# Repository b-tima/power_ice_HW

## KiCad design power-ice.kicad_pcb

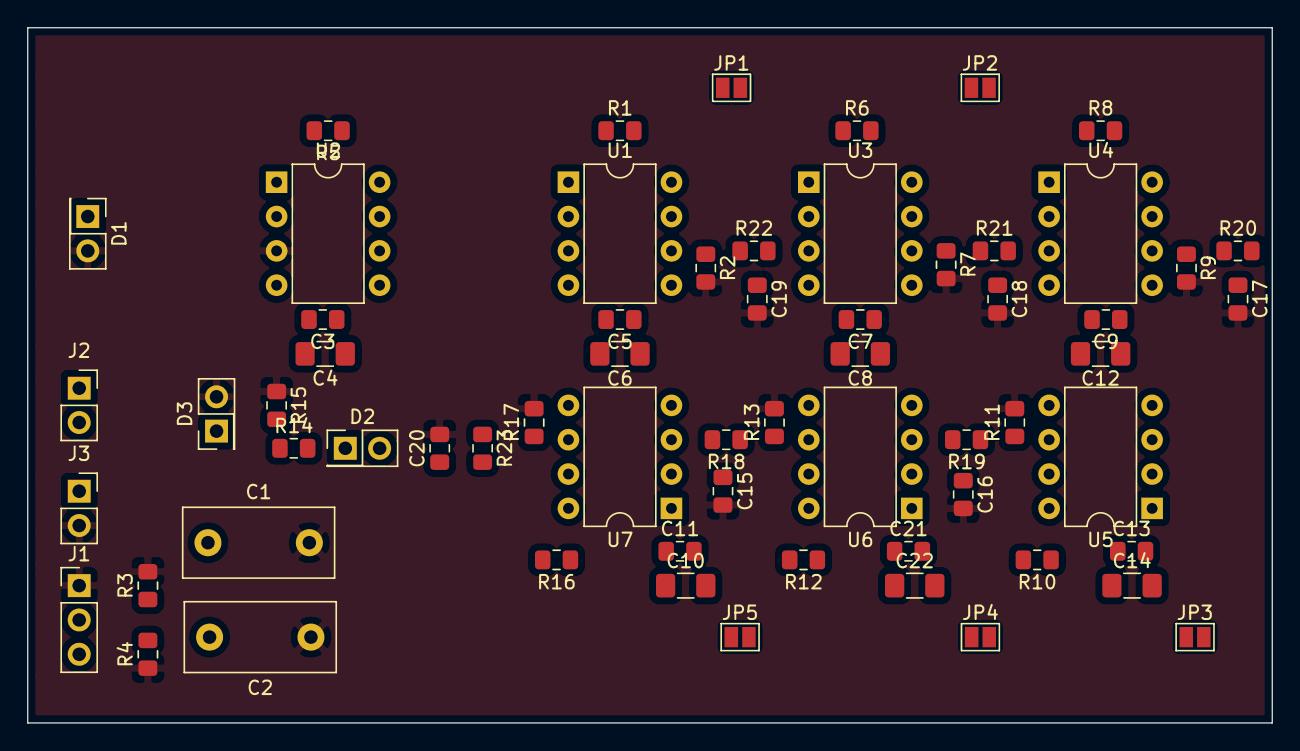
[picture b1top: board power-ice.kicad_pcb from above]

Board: 2 copper layers, 92.1 x 51.4 mm, 63 parts (0 on the bottom side), 25 nets, no tracks yet.

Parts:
C1, C2: 220u; C_Disc_D11.0mm_W5.0mm_P7.50mm
C3, C5, C7, C9, C11, C13, C21: 100n; C_0805_2012Metric_Pad1.15x1.40mm_HandSolder
C4, C6, C8, C10, C12, C14, C22: 1n; C_1206_3216Metric_Pad1.42x1.75mm_HandSolder
C15, C16, C17, C18, C19, C20: C; C_0805_2012Metric_Pad1.15x1.40mm_HandSolder
D1: D_Photo; PinHeader_2x01_P2.54mm_Vertical
D2: D_Schottky; PinHeader_2x01_P2.54mm_Vertical
D3: 3.3V; PinHeader_2x01_P2.54mm_Vertical
J1: Conn_01x03_Female; PinHeader_1x03_P2.54mm_Vertical
J2, J3: Conn_01x02_Female; PinSocket_1x02_P2.54mm_Vertical
JP1, JP2, JP3, JP4, JP5: Jumper; SolderJumper-2_P1.3mm_Open_Pad1.0x1.5mm
R1, R6, R8, R10, R12, R16: 1k; R_0805_2012Metric_Pad1.15x1.40mm_HandSolder
R2, R5, R7, R9, R11, R13, R15, R17: 10k; R_0805_2012Metric_Pad1.15x1.40mm_HandSolder
R3, R4: 4.7k; R_0805_2012Metric_Pad1.15x1.40mm_HandSolder
R14: 22k; R_0805_2012Metric_Pad1.15x1.40mm_HandSolder
R18, R19, R20, R21, R22, R23: R; R_0805_2012Metric_Pad1.15x1.40mm_HandSolder
U1, U2, U3, U4, U5, U6, U7: LM318N; DIP-8_W7.62mm

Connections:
+10V: C1.1, C3.1, C4.1, C5.1, C6.1, C7.1, C8.1, C9.1, C10.1, C11.1, C12.1, C13.1, C14.1, C21.1, C22.1, J1.3, J2.2, R3.1, U1.7, U2.7, U3.7, U4.7, U5.7, U6.7, U7.7
-10V: C2.2, C3.2, C4.2, C5.2, C6.2, C7.2, C8.2, C9.2, C10.2, C11.2, C12.2, C13.2, C14.2, C21.2, C22.2, J1.2, J2.1, R4.2, U1.4, U2.4, U3.4, U4.4, U5.4, U6.4, U7.4
/cascade_filter/in: JP4.2, JP5.1, R12.2, R13.1, R18.1, U6.6
/cascade_filter/out: C15.1, R18.2, U7.3
/sheet6215D380/in: JP3.2, JP4.1, R10.2, R11.1, R19.1, U5.6
/sheet6215D380/out: C16.1, R19.2, U6.3
/sheet6216EEAD/in: JP1.1, R1.2, R2.1, R22.1, U1.6
/sheet6216EEAD/out: C19.1, R22.2, U3.3
/sheet62181AF4/in: JP5.2, R16.2, R17.1, R23.1, U7.6
/sheet621688F6/in: JP1.2, JP2.1, R6.2, R7.1, R21.1, U3.6
/sheet621688F6/out: C18.1, R21.2, U4.3
/sheet62163674/in: JP2.2, JP3.1, R8.2, R9.1, R20.1, U4.6
/sheet62163674/out: C17.1, R20.2, U5.3
GND: C1.2, C2.1, C15.2, C16.2, C17.2, C18.2, C19.2, C20.2, D1.2, D3.2, J1.1, J3.2, R2.2, R3.2, R4.1, R7.2, R9.2, R11.2, R13.2, R15.1, R17.2, U2.3
unnamed: D1.1, R5.2, U2.2
unnamed: D2.1, R14.2
unnamed: D3.1, J3.1, R14.1, R15.2
unnamed: R1.1, U1.2
unnamed: R6.1, U3.2
unnamed: R8.1, U4.2
unnamed: R10.1, U5.2
unnamed: R12.1, U6.2
unnamed: R16.1, U7.2
amp_out: C20.1, D2.2, R23.2
op_cascade_in: R5.1, U1.3, U2.6

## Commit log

2022-02-17 added files
2022-03-06 redesign
